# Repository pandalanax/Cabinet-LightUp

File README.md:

# Cabinet-LightUp

## Components
- WS2812 Strip with 30 LEDs
- Reed Switch
- Arduino Nano 
- MCP1700 LDO 
- 2N3904 Transistor
- 1N4007 Diode
- 100NF Cap
- 2x 1µF Cap
- 1k Ohm Resistor
- 3x AA Battery
- 1 Battery Case

## Arduino Nano Modifications
After Modification, the usage of the USB port of the Nano could damage it. I program the Nano via ICSP Pins with 3.3v.

#### Core
The Core was changed to [Minicore](https://github.com/MCUdude/MiniCore). Underclocked the Nano to 8Mhz using internal oscillator. 
#### LED
Removed the Resistor for the POWER led.
#### Voltage Regulator
The nanos voltage regulator uses a lot of energy, therefore i removed the regulator and changed it to a LDO MCP1700

## Circuit
Using the transistor alone didn't help to completely shut down the WS2812 strip. Found this helpful [thread](https://forum.pjrc.com/threads/24407-Strange-WS2812-NeoPixel-backfeed-current-FYIO) which suggested using a diode to eliminate the backfeeding problem through DATA channel.

## Current Draw Measurement
The current is measured with an external Arduino Nano and INA219 Breakout Board.

# TODO

- [x] add schematic
- [x] create pcb
- [ ] upload hex file to flash via avrdude 
- [ ] upload minicore settings to flash via avrdude

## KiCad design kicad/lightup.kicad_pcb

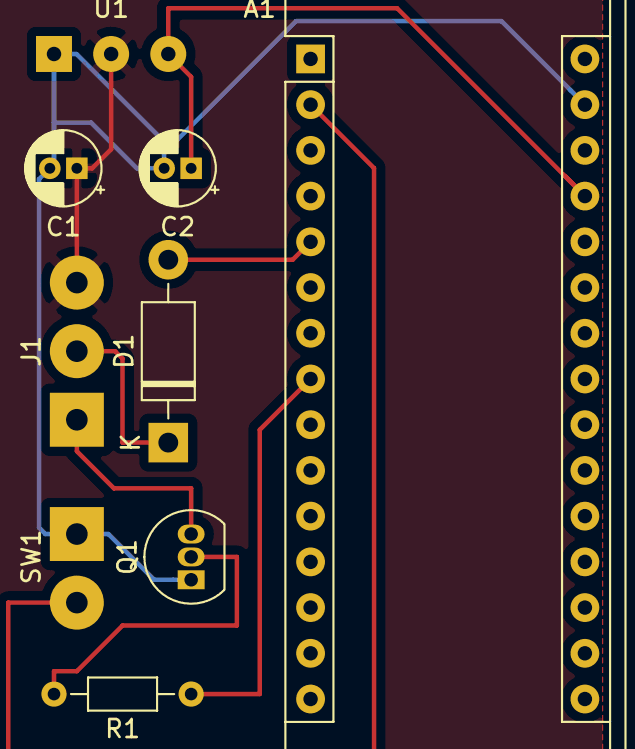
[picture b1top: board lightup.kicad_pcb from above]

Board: 2 copper layers, 9 parts (0 on the bottom side), 9 nets.

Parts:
A1: Arduino_Nano_v2.x; Arduino_Nano
C1, C2: 1uF; CP_Radial_D4.0mm_P1.50mm
D1: 1N4007; D_DO-41_SOD81_P10.16mm_Horizontal
J1: WS2812; SolderWirePad_1x03_P3.81mm_Drill1.2mm
Q1: 2N3904; TO-92_Inline
R1: R_US; R_Axial_DIN0204_L3.6mm_D1.6mm_P7.62mm_Horizontal
SW1: SW_Reed; SolderWirePad_1x02_P3.81mm_Drill1.2mm
U1: MCP1700-3302E_TO92; SolderWirePad_1x03_P3.175mm_Drill0.8mm

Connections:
+4V: C1.1, J1.3, U1.2
GND: A1.29, C1.2, C2.2, Q1.1, SW1.1, U1.1
unnamed: A1.2, SW1.2
unnamed: A1.5, D1.2
unnamed: A1.8, R1.1
unnamed: A1.27, C2.1, U1.3
unnamed: D1.1, J1.2
unnamed: J1.1, Q1.3
unnamed: Q1.2, R1.2

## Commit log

2021-09-13 init
2021-09-13 added kicad files
2021-10-13 got confused with pins - fixed
